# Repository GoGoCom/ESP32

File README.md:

# ESP32

## Introduction

I created a heater temperature control system using Blynk and an ESP32. The ESP32 is a powerful device with WiFi and Bluetooth capabilities. By combining these two, I created an IoT system that allows remote heaters to be turned on and off at specific temperatures and time periods.
This sketch is implemented provisioning using BLE as the mode of transport for provisioning-related communication between the device (to be provisioned) and the client (owner of the device).

## Provisioning Tools

### Provisioning using BLE
```

Provisioning started
Give Credentials of your access point using  of "Android app" or "apple asp" ESP BLE Prov.

Received Wi-Fi credentials
    SSID: your own ssid
    Password: your own password

Connected IP address: 192.168.43.120
Provisioning Successful
Provisioning Ends
```

## Blynk Tools

[Blynk](https://www.blynk.io/) is an excellent platform for solving IoT problems.It is the most powerful tool when you want to control something on the Internet, whether it is on mobile or PC.
By defining the required streams in the Blynk.Console and connecting them to components, you can exchange data over the network.
You must first sign up on https://blynk.cloud/dashboard/login  before you can use it.

After defining the device and setting up the development template through the Blynk console, find out the following three values and enter them at the beginning of the source code: BLYNK TEMPLATE ID, BLYNK TEMPLATE_NAME, and BLYNK AUTHTOKEN.

| define |
|-|
|#define BLYNK_TEMPLATE_ID  "XMgt6fqp4aXvb" |
|#define BLYNK_TEMPLATE_NAME  "TempControl" |
|#define BLYNK_AUTH_TOKEN  "0f0ffASdldldleefeeXXiCNCvQT3Ff3H" |

### Blynk App / Display

## Library
| Library | version | description |
|-|-|-|
| Blynk | 1.3.2 | IoT |
| ESP8266 and ESP32 OLED driver foe SSSD1306 | 4.6.2 | display |
| DallasTemperature | 4.0.5 | temperature sensor  |
| Onewire | 2.3.8 | One wire commucarion  |
| Time | 1.6.1 | date and time  |
| OneButton | 2.6.1 | button switch  |

## Tool
| Tool | version | description |
|-|-|-|
| Autodesk Eagle | 9.6.2 | hardware |
| Autodesk Fusion |     | case desin for 3D printing |
| Arduino IDE | 2.3.7 | software |

## Acknowledgments

I would like to thank to every one for their contributions.

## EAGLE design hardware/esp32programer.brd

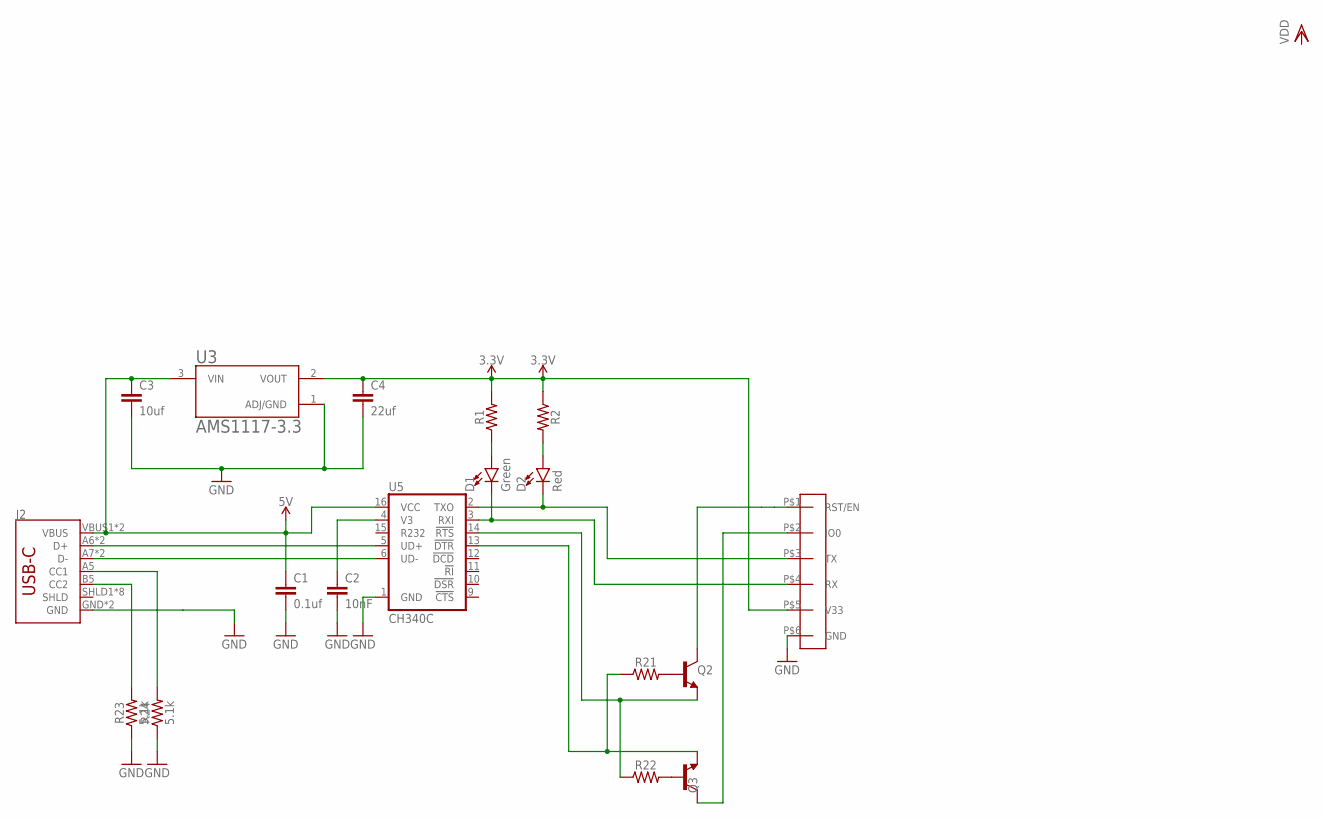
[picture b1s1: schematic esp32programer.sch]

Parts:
C1: 0.1uf; 0805
C2: 10nF; 0805
C3: 10uf; 0805
C4: 22uf; 0805
D1: Green; LED-0805
D2: Red; LED-0805
J2: USB_C16PIN; USB-C-16P
Q2, Q3: TRANSISTOR_BJT_NPN-SOT-23-BEC; SOT-23
R1, R2, R21, R22: 0805
R23, R24: 5.1k; 0805
U3: AMS1117-3.3; SOT229P700X180-4N
U5: CH340C; SO016
U$6: USBCOUT; 6PINS

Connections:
3.3V: C4.1, R1.2, R2.1, U3.2 (VOUT), U$6.P$5 (V33)
5V: C1.1, C3.1, J2.VBUS1 (VBUS), J2.VBUS2 (VBUS), U3.3 (VIN), U5.16 (VCC)
!DTR: Q3.2 (E), R21.1, U5.13 (!DTR)
CC2: J2.B5 (CC2), R23.2
D+: J2.A6 (D+), J2.B6 (D+), U5.5 (UD+)
D-: J2.A7 (D-), J2.B7 (D-), U5.6 (UD-)
GND: C1.2, C2.2, C3.2, C4.2, J2.GND, J2.GND2 (GND), R23.1, R24.1, U3.1 (ADJ/GND), U5.1 (GND), U$6.P$6 (GND)
unnamed: D1.C, U5.3 (RXI), U$6.P$4 (RX)
unnamed: C2.1, U5.4 (V3)
unnamed: D1.A, R1.1
unnamed: D2.A, R2.2
unnamed: Q2.3 (C), U$6.P$1 (RST/EN)
unnamed: Q3.3 (C), U$6.P$2 (IO0)
unnamed: Q2.2 (E), R22.1, U5.14 (!RTS)
unnamed: Q2.1 (B), R21.2
unnamed: Q3.1 (B), R22.2
unnamed: J2.A5 (CC1), R24.2
RXI: D2.C, U5.2 (TXO), U$6.P$3 (TX)

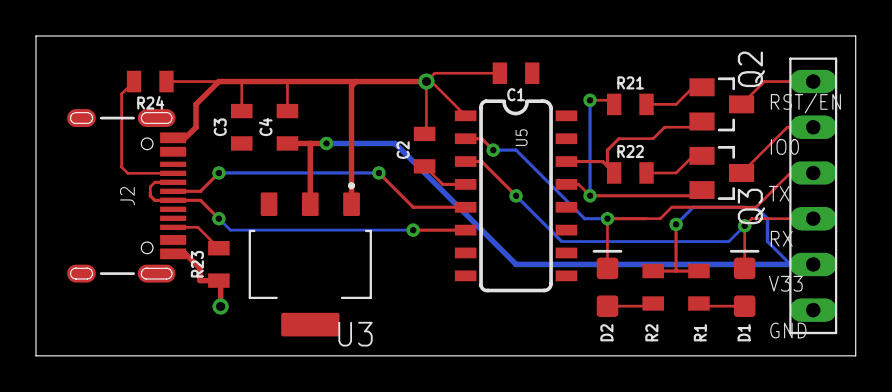
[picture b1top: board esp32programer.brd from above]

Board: 2 copper layers, 45.5 x 17.8 mm, 18 parts (0 on the bottom side), 18 nets.

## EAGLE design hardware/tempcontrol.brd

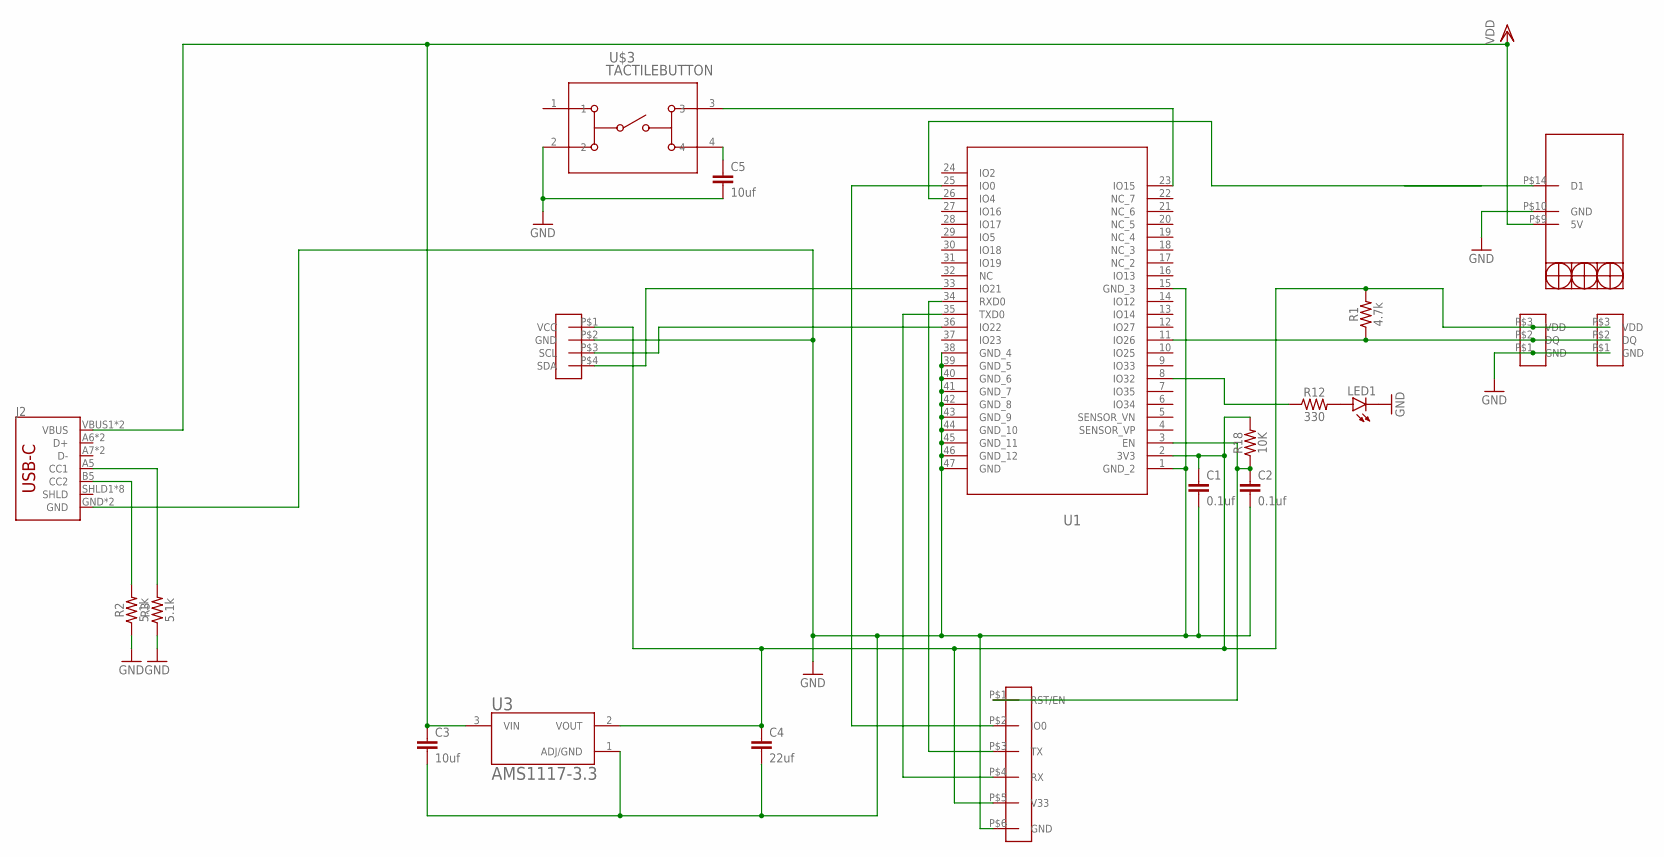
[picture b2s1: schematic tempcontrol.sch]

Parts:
C1, C2: 0.1uf; 0805
C3, C5: 10uf; 0805
C4: 22uf; 0805
J2: USB_C16PIN; USB-C-16P
LED1: LEDSML0805; SML0805
R1: 4.7k; 0805
R2, R3: 5.1k; 0805
R12: 330; 0805
R18: 10K; 0805
U1: ESP32-WROOM-32E_(4MB)ESP32�WROOM�32E_EXP; ESP32�WROOM�32E_EXP
U3: AMS1117-3.3; SOT229P700X180-4N
U$1: RELAYMINI; 16PINSWIDE
U$2, U$4: DS18B20TR; 3PINS
U$3: TACTILEBUTTON; TACTILEPINS
U$5: USBCOUT; 6PINS
U$18: OLEDVCC; OLEPINS

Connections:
3V3: C1.1, C4.1, R1.2, R18.2, U1.2 (3V3), U3.2 (VOUT), U$2.P$3 (VDD), U$4.P$3 (VDD), U$5.P$5 (V33), U$18.P$1 (VCC)
CC2: J2.B5 (CC2), R2.2
GND: C1.2, C2.2, C3.2, C4.2, C5.2, J2.GND, J2.GND2 (GND), LED1.C, R2.1, R3.1, U1.1 (GND_2), U1.15 (GND_3), U1.38 (GND_4), U1.39 (GND_5), U1.40 (GND_6), U1.41 (GND_7), U1.42 (GND_8), U1.43 (GND_9), U1.44 (GND_10), U1.45 (GND_11), U1.46 (GND_12), U1.47 (GND), U3.1 (ADJ/GND), U$1.P$10 (GND), U$2.P$1 (GND), U$3.2, U$4.P$1 (GND), U$5.P$6 (GND), U$18.P$2 (GND)
unnamed: U1.26 (IO4), U$1.P$14 (D1)
unnamed: C5.1, U$3.4
unnamed: J2.A5 (CC1), R3.2
unnamed: U1.23 (IO15), U$3.3
unnamed: R1.1, U1.11 (IO26), U$2.P$2 (DQ), U$4.P$2 (DQ)
unnamed: LED1.A, R12.2
unnamed: C2.1, R18.1, U1.3 (EN), U$5.P$1 (RST/EN)
unnamed: U1.25 (IO0), U$5.P$2 (IO0)
unnamed: U1.33 (IO21), U$18.P$4 (SDA)
unnamed: U1.35 (TXD0), U$5.P$4 (RX)
unnamed: U1.36 (IO22), U$18.P$3 (SCL)
unnamed: U1.34 (RXD0), U$5.P$3 (TX)
unnamed: R12.1, U1.8 (IO32)
VDD: C3.1, J2.VBUS1 (VBUS), J2.VBUS2 (VBUS), U3.3 (VIN), U$1.P$9 (5V)

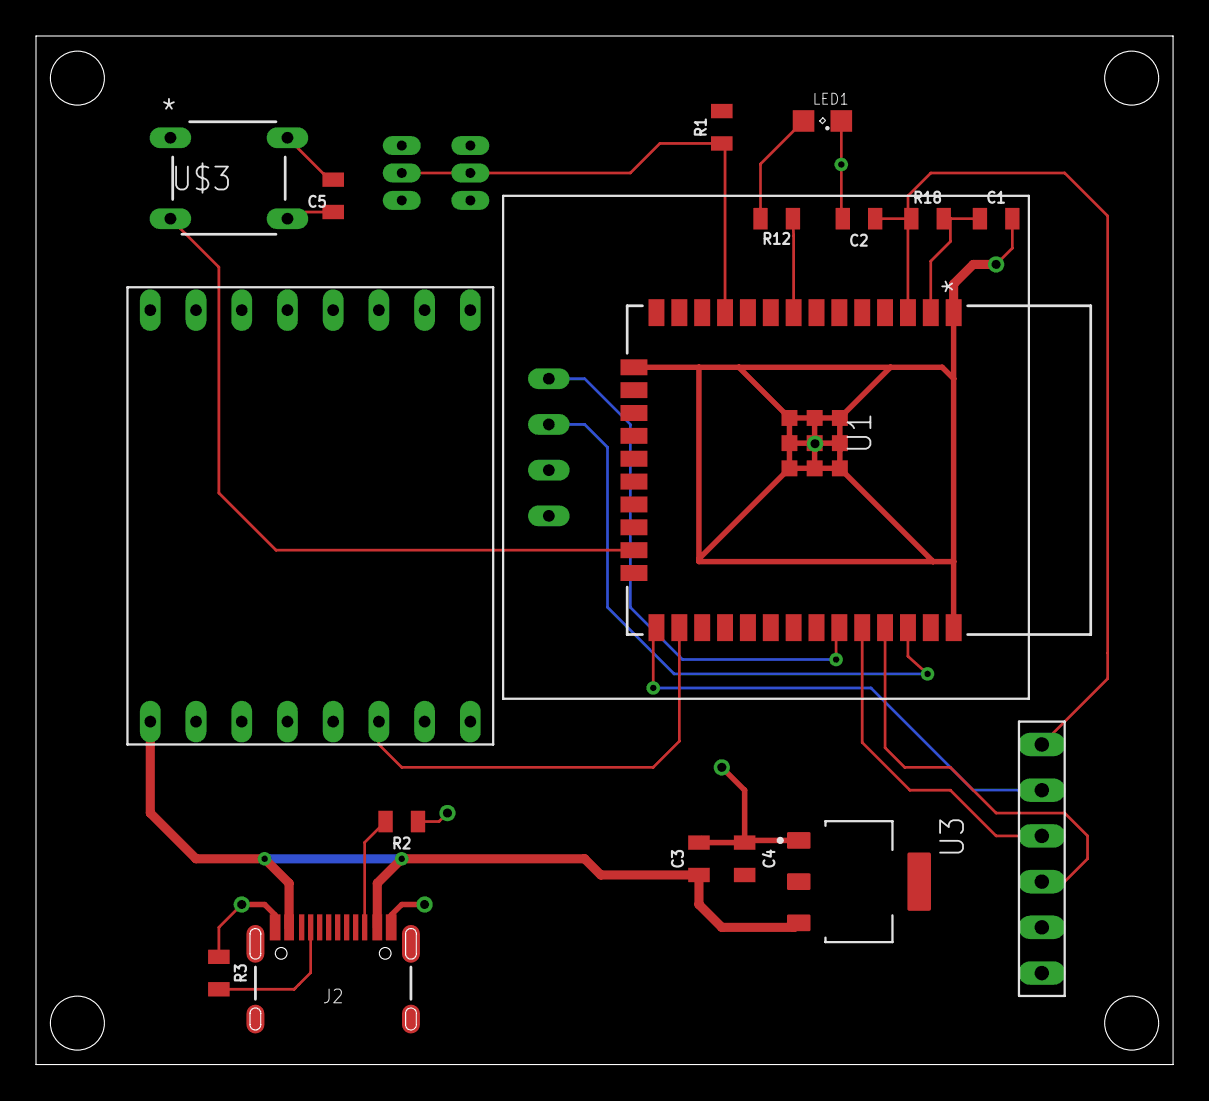
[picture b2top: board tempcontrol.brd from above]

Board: 2 copper layers, 63.2 x 57.1 mm, 20 parts (0 on the bottom side), 17 nets.

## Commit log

2026-01-15 upload

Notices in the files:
parts and their libraries:
SparkFun-Resistors: Licensing: Creative Commons ShareAlike 4.0 International - https://creativecommons.org/licenses/by-sa/4.0
COPYRIGHT: Copyright (C) 2024 Ultra Librarian. All rights reserved.
